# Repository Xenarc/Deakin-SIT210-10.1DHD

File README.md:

# Deakin-SIT210-10.1DHD
Public Repository for task 10.1DHD for unit SIT210 undertaken at Deakin University

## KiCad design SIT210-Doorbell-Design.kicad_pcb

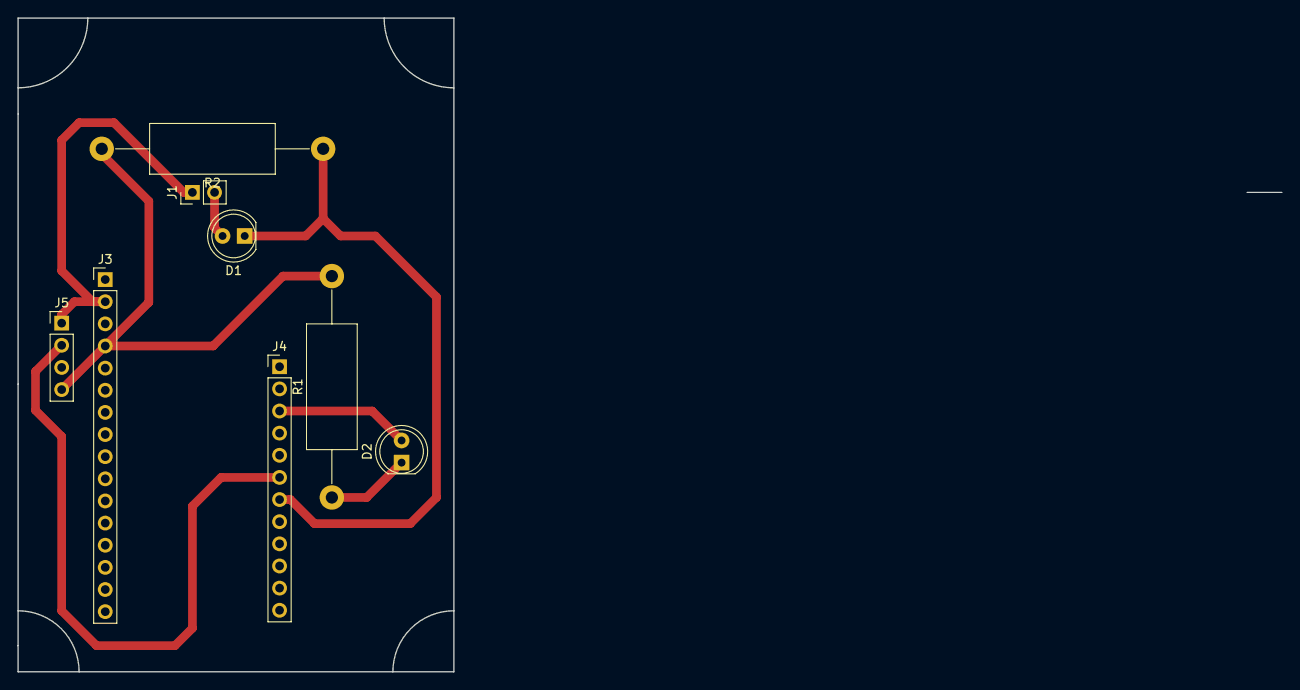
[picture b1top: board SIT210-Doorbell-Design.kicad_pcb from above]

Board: 2 copper layers, 145.0 x 75.0 mm, 8 parts (0 on the bottom side), 7 nets.

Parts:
D1, D2: LED; LED_D5.0mm
J1: Pin_Header_Straight_1x02_Pitch2.54mm
J3: Particle; Pin_Header_Straight_1x16_Pitch2.54mm
J4: Interconnect; Pin_Header_Straight_1x12_Pitch2.54mm
J5: DHT22; Pin_Header_Straight_1x04_Pitch2.54mm
R1, R2: 270R; R_Axial_DIN0614_L14.3mm_D5.7mm_P25.40mm_Horizontal

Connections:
+3V3: J1.1, J3.2, J5.1
GND: J3.4, J5.4, R1.2, R2.2
unnamed: D1.1, J4.7, R2.1
unnamed: D1.2, J1.2
unnamed: D2.1, R1.1
unnamed: D2.2, J4.3
unnamed: J4.6, J5.2
